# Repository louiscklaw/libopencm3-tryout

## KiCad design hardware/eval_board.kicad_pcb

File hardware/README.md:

### check list
debug port
screen text painting

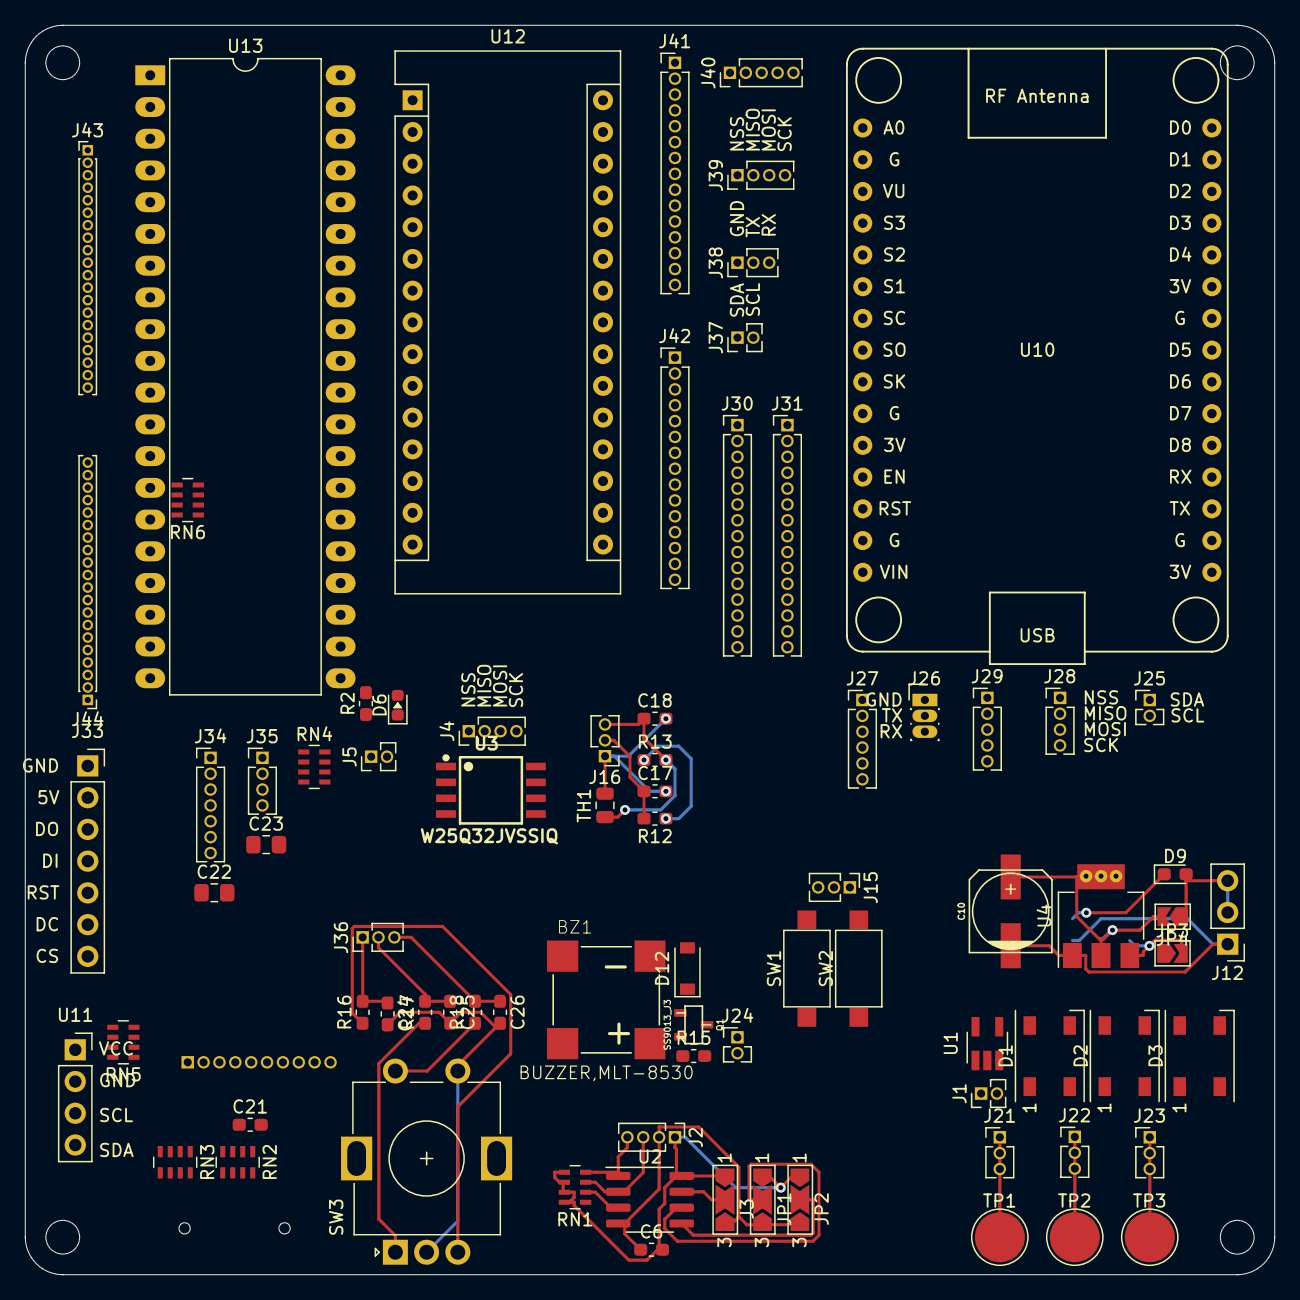
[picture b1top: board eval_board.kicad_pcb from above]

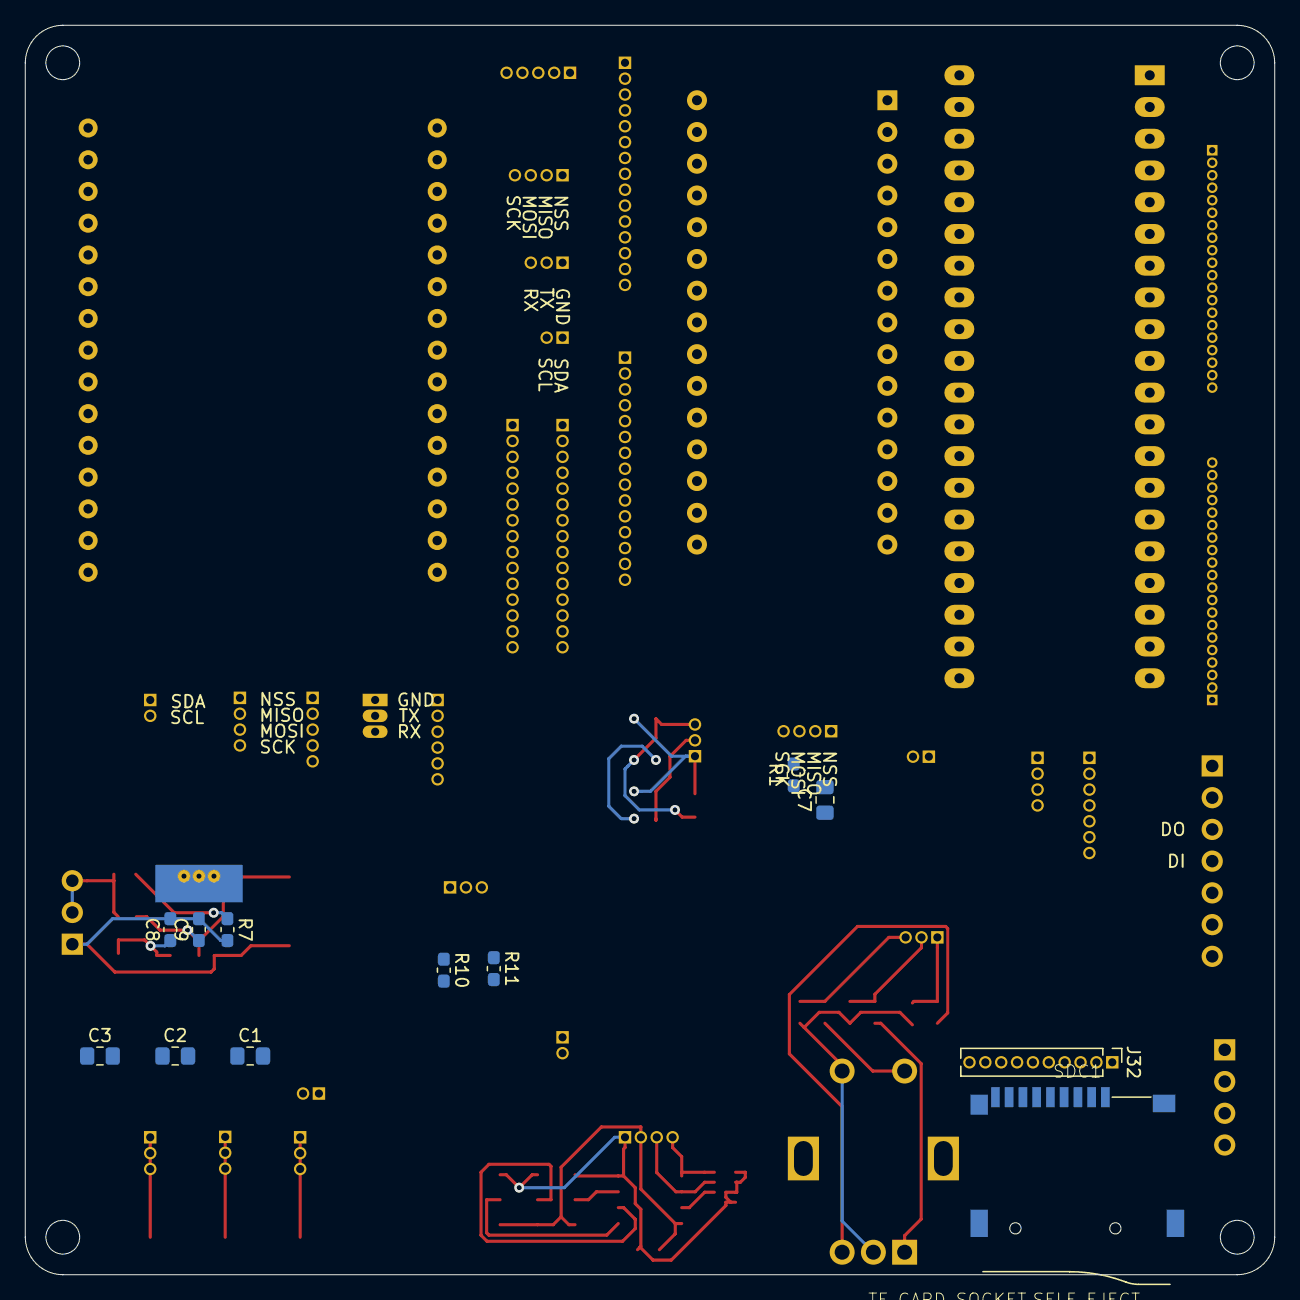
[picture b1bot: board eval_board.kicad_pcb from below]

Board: 2 copper layers, 100.0 x 100.0 mm, 97 parts (12 on the bottom side), 91 nets.

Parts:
BZ1: BUZZER,MLT-8530; MLT-8530
C1, C2, C3, C7, C22, C23: C106,0805; C_0805_2012Metric_Pad1.15x1.40mm_HandSolder
C6, C17, C18: C106,0603; C_0603_1608Metric_Pad1.05x0.95mm_HandSolder
C8, C9, C24, C25, C26: C104,0603; C_0603_1608Metric_Pad1.05x0.95mm_HandSolder
C10: CP47uf,50V; c_elec_6.3x7.7
C21: C475,0805; C_0603_1608Metric_Pad1.05x0.95mm_HandSolder
D1, D2, D3: WS2812B; LED_WS2812B_PLCC4_5.0x5.0mm_P3.2mm
D6: LED_GREEN,0603; LED_0603_1608Metric
D9: LED_GREEN,0603; LED_0603_1608Metric_Pad1.05x0.95mm_HandSolder
D12: D_1N4148_T4; D_SOD-123
H1, H2, H3, H4: MountingHole; MountingHole_2.7mm_M2.5,rpi_like
J1: WS2812_HEADER; PinHeader_1x02_P1.27mm_Vertical
J2, J35: OLED_I2C_HEADER; PinHeader_1x04_P1.27mm_Vertical
J3: A0_SEL; SolderJumper-3_P2.0mm_Open_TrianglePad1.0x1.5mm_NumberLabels
J4, J28, J39: SPI_HEADER; SPI_DEBUG
J5: BLINK_HEADER; PinHeader_1x02_P1.27mm_Vertical
J12: Conn_01x03; PinHeader_1x03_P2.54mm_Vertical
J15: BTN_HEADER; PinHeader_1x03_P1.27mm_Vertical
J16: ADC_HEADER; PinHeader_1x03_P1.27mm_Vertical
J21: GND; PinHeader_1x03_P1.27mm_Vertical
J22: 5V; PinHeader_1x03_P1.27mm_Vertical
J23: 3V3; PinHeader_1x03_P1.27mm_Vertical
J24: BUZZER_HEADER; PinHeader_1x02_P1.27mm_Vertical
J25: I2C_DEBUG
J26: TTL_HEADER; TTL_TERMINAL_1.27mm
J27: SDCARD_HEADER
J29, J40: OLED_HEADER; PinHeader_1x05_P1.27mm_Vertical
J30: NODEMCU_HEADER1; PinHeader_1x15_P1.27mm_Vertical
J31: NODEMCU_HEADER2; PinHeader_1x15_P1.27mm_Vertical
J32: sdcard_header; SDCARD_HEADER_10PIN
J33: SSD1306-OLED-SPI; CONN_SPI_SSD1306
J34: OLED_SPI_HEADER; PinHeader_1x07_P1.27mm_Vertical
J36: ROT_ENC_HEADER; PinHeader_1x03_P1.27mm_Vertical
J37: I2C_HEADER; I2C_DEBUG
J38: TTL_HEADER
J41: ARDUINO_HEADER1; PinHeader_1x15_P1.27mm_Vertical
J42: ARDUINO_HEADER2; PinHeader_1x15_P1.27mm_Vertical
J43: STM32_2_DEBUG1; PinHeader_1x20_P1.00mm_Vertical
J44: STM32_2_DEBUG2; PinHeader_1x20_P1.00mm_Vertical
JP1: A1_SEL; SolderJumper-3_P2.0mm_Open_TrianglePad1.0x1.5mm_NumberLabels
JP2: A2_SEL; SolderJumper-3_P2.0mm_Open_TrianglePad1.0x1.5mm_NumberLabels
JP3: PWR_SRC; SolderJumper-2_P1.3mm_Open_TrianglePad1.0x1.5mm
JP4: PWR_OUT; SolderJumper-2_P1.3mm_Open_TrianglePad1.0x1.5mm
Q1: SS9013_J3; 9013,J3,SOT23
R1, R10, R11: R103,0603; R_0603_1608Metric_Pad1.05x0.95mm_HandSolder
R2, R15: R471,0603; R_0603_1608Metric_Pad1.05x0.95mm_HandSolder
R7: R102,0603; R_0603_1608Metric_Pad1.05x0.95mm_HandSolder
R12, R13: R472,0603; R_0603_1608Metric_Pad1.05x0.95mm_HandSolder
R16, R17, R18: R273,0603; R_0603_1608Metric_Pad1.05x0.95mm_HandSolder
RN1, RN2, RN3, RN4, RN5, RN6: R_Pack04; R_Array_Concave_4x0603
SDC1: TF_CARD_SOCKET,SELF_EJECT; SUNTECH_ST-TF-003A
SW1, SW2: SW_RESET,2_leg,SMD; SW_SPST_CK_RS282G05A3
SW3: EC11_VERTICAL; RotaryEncoder_Alps_EC11E_Vertical_H20mm
TH1: Thermistor_NTC,0805; R_0805_2012Metric
TP1, TP2, TP3: TestPoint; TestPoint_Pad_D4.0mm
U1: 74AHCT1G125; SOT-23-5_HandSoldering
U2: LM75; SOP-8_3.76x4.96mm_P1.27mm
U3: W25Q32JVSSIQ
U4: AMS1117-3.3; AMS1117_SOT-223
U10: nodemcu; NodeMCU1.0(12-E)
U11: SSD1306-OLED-I2C; CONN_I2C_SSD1306
U12: arduino_nano_v3; Arduino_Nano
U13: bluepill-stm32f103c8t6; DIP-40_W15.24mm_LongPads

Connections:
+3V3: BZ1.P, C6.2, C7.2, C21.1, C22.2, C23.2, D9.2, D12.1, J2.1, J3.1, J12.2, J12.3, J23.1, J23.2, J23.3, J30.11, J31.6, J31.15, J32.VDD, J33.5V, J34.1, J35.1, J43.18, J44.1, JP1.1, JP2.1, JP4.1, R1.1, R2.1, R10.1, R12.1, R13.1, RN1.5, RN1.6, RN1.7, RN1.8, RN2.5, RN2.6, RN2.7, RN2.8, RN3.5, RN3.6, RN3.7, RN3.8, RN4.5, RN4.6, RN4.7, RN4.8, RN5.5, RN5.6, RN5.7, RN5.8, RN6.5, RN6.6, RN6.7, RN6.8, SDC1.4, SW1.2, TP3.1, U2.8, U3.3, U3.7, U3.8, U10.11, U10.16, U10.25, U11.VCC, U13.20, U13.38
+5V: C1.2, C2.2, C3.2, D1.1, D2.1, D3.1, J22.1, J22.2, J22.3, J42.1, J42.4, J44.3, TP2.1, U1.5, U12.27, U12.30, U13.18
/A_IN0: C17.1, J16.2, J43.5, R12.2, U13.25
/A_IN1: C18.1, J16.3, J43.6, R13.2, TH1.1, U13.26
/BTN_PULL_DN: J15.3, J43.8, R11.2, SW1.1, U13.28
/BTN_PULL_UP: J15.2, J43.13, R10.2, SW2.1, U13.33
/BUZZER_IN: J24.1, J44.13, R15.2, U13.8
/DEBUG_LED: D6.1, J5.2, J44.9, U13.12
/LORA_DIO0: J44.16, U13.5
/LORA_RST: J44.18, U13.3
/MISO: J4.MISO, J28.MISO, J31.9, J39.MISO, J41.15, J43.11, U3.2, U10.22, U12.15, U13.31
/MOSI: J4.MOSI, J28.MOSI, J29.1, J31.10, J33.DI, J34.4, J39.MOSI, J40.1, J41.14, J43.12, RN4.4, U3.5, U10.21, U12.14, U13.32
/OLED_DC: J33.DC, J34.6, J43.14, RN4.3, U13.34
/OLED_RST: J33.RST, J34.5, J44.8, U13.13
/PWM_IN: J44.11, U13.10
/ROT_ENC_A: C24.1, J36.1, J44.5, R16.2, U13.16
/ROT_ENC_B: C25.1, J36.2, J44.4, R17.2, U13.17
/ROT_ENC_SW: C26.1, J36.3, J43.15, R18.2, U13.35
/RX: J44.14, U13.7
/SCK: J4.SCK, J28.SCK, J29.2, J31.8, J33.DO, J34.3, J39.SCK, J40.2, J42.15, J43.10, RN4.2, U3.6, U10.23, U12.16, U13.30
/SCL: J2.3, J25.SCL, J31.2, J35.3, J37.SCL, J42.7, J44.7, RN1.3, RN5.2, RN6.2, U2.2, U10.29, U11.SCL, U12.24, U13.14
/SDA: J2.4, J25.SDA, J31.1, J37.SDA, J42.8, J44.6, RN1.4, RN6.1, U2.1, U10.30, U12.23, U13.15
/SDCLK: J27.SDCLK, J30.9, J32.CLK, RN2.2, SDC1.5, U10.9
/SDCMD: J27.SDCMD, J30.7, J32.CMD, RN2.4, SDC1.3, U10.7
/SDD0: J27.SDD0, J30.8, J32.DAT0, RN3.2, SDC1.7, U10.8
/SDD1: J27.SDD1, J30.6, J32.CAT1, RN3.1, SDC1.8, U10.6
/SDD2: J27.SDD2, J30.5, J32.DAT2, RN3.4, SDC1.1, U10.5
/SDD3: J27.SDD3, J30.4, J32.DAT3, RN3.3, SDC1.2, U10.4
/SS_ARDUINO: J39.NSS, J41.13, J44.19, U12.13, U13.2
/SS_ESP: J28.NSS, J31.11, J44.20, U10.20, U13.1
/SS_LORA: J44.12, U13.9
/SS_OLED: J33.CS, J34.7, J44.10, RN4.1, U13.11
/SS_STM32: J43.9, U13.29
/SS_W25Q32: J4.NSS, J44.17, R1.2, U3.1, U13.4
/TX: J44.15, U13.6
/WS2812_OUT: J1.2, J43.16, U1.2, U13.36
/arduino_nano/3V3: J42.14, U12.17
/arduino_nano/A0: J42.12, U12.19
/arduino_nano/A1: J42.11, U12.20
/arduino_nano/A2: J42.10, U12.21
/arduino_nano/A3: J42.9, U12.22
/arduino_nano/A6: J42.6, U12.25
/arduino_nano/A7: J42.5, U12.26
/arduino_nano/AREF: J42.13, U12.18
/arduino_nano/D0: J38.RX, J41.2, U12.2
/arduino_nano/D1: J38.TX, J41.1, U12.1
/arduino_nano/D2: J41.5, U12.5
/arduino_nano/D3: J41.6, U12.6
/arduino_nano/D7: J41.10, U12.10
/arduino_nano/D8: J41.11, U12.11
/arduino_nano/D9: J41.12, U12.12
/arduino_nano/OLED_DC: J40.3, J41.7, U12.7
/arduino_nano/OLED_RST: J40.4, J41.8, U12.8
/arduino_nano/OLED_SS: J40.5, J41.9, U12.9
/arduino_nano/RST: J41.3, J42.3, U12.3, U12.28
/bluepill/NRST: J43.17, U13.37
/bluepill/PA2: J43.7, U13.27
/bluepill/PC13: J43.2, U13.22
/bluepill/PC14: J43.3, U13.23
/bluepill/PC15: J43.4, U13.24
/bluepill/VBAT: J43.1, U13.21
/nodemcu/A0: J30.1, U10.1
/nodemcu/EN: J30.12, U10.12
/nodemcu/OLED_DC: J29.3, J31.3, U10.28
/nodemcu/OLED_RST: J29.4, J31.4, U10.27
/nodemcu/OLED_SS: J29.5, J31.5, U10.26
/nodemcu/RST: J30.13, U10.13
/nodemcu/RSV_2: J30.2, U10.2
/nodemcu/RSV_3: J30.3, U10.3
/nodemcu/RX: J26.RX, J31.12, U10.19
/nodemcu/TX: J26.TX, J31.13, U10.18
/nodemcu/VIN: J30.15, U10.15
/oled.sch/OLED_I2C_SDA: J35.4, RN5.1, U11.SDA
GND: C1.1, C2.1, C3.1, C6.1, C7.1, C8.2, C9.2, C10.2, C17.2, C18.2, C21.2, C22.1, C23.1, C24.2, C25.2, C26.2, D1.3, D2.3, D3.3, J1.1, J2.2, J3.3, J5.1, J12.1, J15.1, J16.1, J21.1, J21.2, J21.3, J24.2, J26.GND, J30.10, J30.14, J31.7, J31.14, J32.GND, J32.VSS, J33.GND, J34.2, J35.2, J38.GND, J41.4, J42.2, J43.19, J43.20, J44.2, JP1.3, JP2.3, Q1.2, R7.2, R11.1, SDC1.6, SDC1.G, SW2.2, SW3.C, SW3.E, TH1.2, TP1.1, U1.1, U1.3, U2.4, U3.4, U4.1, U10.10, U10.14, U10.17, U10.24, U11.GND, U12.4, U12.29, U13.19, U13.39, U13.40
unnamed: BZ1.N, D12.2, Q1.3
unnamed: C8.1, JP3.2, U4.3
unnamed: C9.1, C10.1, JP4.2, U4.2
unnamed: D1.2, D2.4
unnamed: D1.4, U1.4
unnamed: D2.2, D3.4
unnamed: D6.2, R2.2
unnamed: D9.1, R7.1
unnamed: J3.2, U2.7
unnamed: J32.CD, SDC1.9
unnamed: JP1.2, U2.6
unnamed: JP2.2, U2.5
unnamed: Q1.1, R15.1
unnamed: R16.1, SW3.B
unnamed: R17.1, SW3.A
unnamed: R18.1, SW3.D
unnamed: RN1.2, U2.3

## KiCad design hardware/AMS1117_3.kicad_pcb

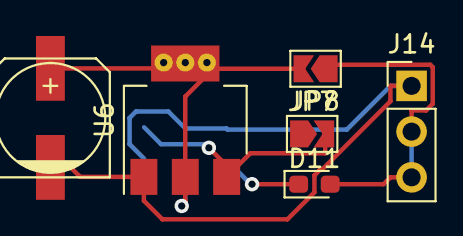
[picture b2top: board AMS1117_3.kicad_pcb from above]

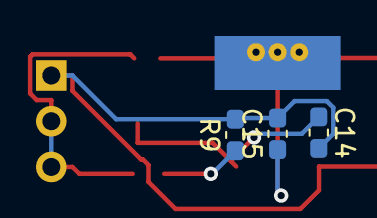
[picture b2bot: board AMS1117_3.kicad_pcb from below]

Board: 2 copper layers, 9 parts (3 on the bottom side), 5 nets.

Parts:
C14, C15: C104,0603; C_0603_1608Metric_Pad1.05x0.95mm_HandSolder
C16: CP47uf,50V; c_elec_6.3x7.7
D11: LED_GREEN,0603; LED_0603_1608Metric_Pad1.05x0.95mm_HandSolder
J14: Va_header; PinHeader_1x03_P2.54mm_Vertical
JP7: PWR_SRC; SolderJumper-2_P1.3mm_Open_TrianglePad1.0x1.5mm
JP8: PWR_OUT; SolderJumper-2_P1.3mm_Open_TrianglePad1.0x1.5mm
R9: R102,0603; R_0603_1608Metric_Pad1.05x0.95mm_HandSolder
U6: AMS1117-3.3; AMS1117_SOT-223

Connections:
GND: C14.2, C15.2, C16.2, J14.1, R9.2, U6.1
unnamed: C14.1, JP7.2, U6.3
unnamed: C15.1, C16.1, JP8.2, U6.2
unnamed: D11.1, R9.1
Vc: D11.2, J14.2, J14.3, JP8.1

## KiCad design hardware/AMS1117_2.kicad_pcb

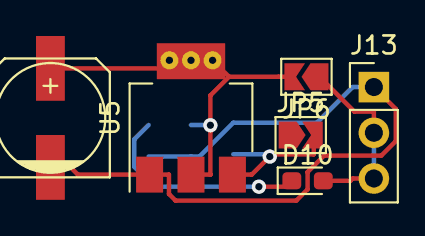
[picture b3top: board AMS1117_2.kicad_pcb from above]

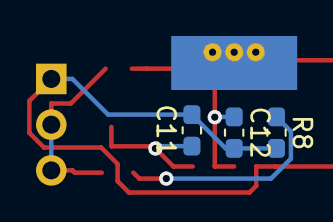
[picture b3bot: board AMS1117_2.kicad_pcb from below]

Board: 2 copper layers, 9 parts (3 on the bottom side), 5 nets.

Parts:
C11, C12: C104,0603; C_0603_1608Metric_Pad1.05x0.95mm_HandSolder
C13: CP47uf,50V; c_elec_6.3x7.7
D10: LED_GREEN,0603; LED_0603_1608Metric_Pad1.05x0.95mm_HandSolder
J13: Conn_01x03; PinHeader_1x03_P2.54mm_Vertical
JP5: PWR_SRC; SolderJumper-2_P1.3mm_Open_TrianglePad1.0x1.5mm
JP6: PWR_OUT; SolderJumper-2_P1.3mm_Open_TrianglePad1.0x1.5mm
R8: R102,0603; R_0603_1608Metric_Pad1.05x0.95mm_HandSolder
U5: AMS1117-3.3; AMS1117_SOT-223

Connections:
GND: C11.2, C12.2, C13.2, J13.1, R8.2, U5.1
unnamed: C11.1, JP5.2, U5.3
unnamed: C12.1, C13.1, JP6.2, U5.2
unnamed: D10.1, R8.1
Vb: D10.2, J13.2, J13.3, JP6.1

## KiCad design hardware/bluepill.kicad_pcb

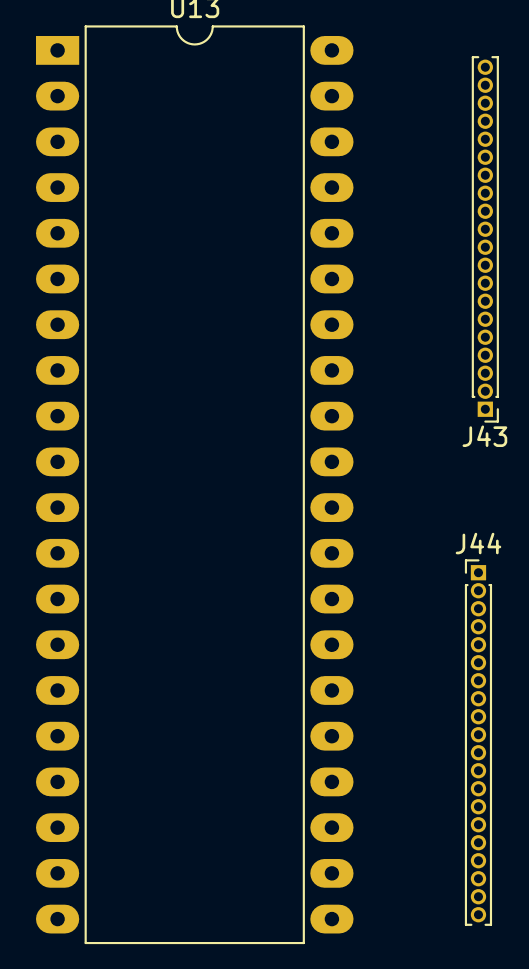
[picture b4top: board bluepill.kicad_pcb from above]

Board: 2 copper layers, 4 parts (1 on the bottom side), 37 nets, no tracks yet.

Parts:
J43: STM32_2_DEBUG1; PinHeader_1x20_P1.00mm_Vertical
J44: STM32_2_DEBUG2; PinHeader_1x20_P1.00mm_Vertical
RN6: R_Pack04; R_Array_Concave_4x0603
U13: bluepill-stm32f103c8t6; DIP-40_W15.24mm_LongPads

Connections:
+3V3: J43.18, J44.1, RN6.5, RN6.6, RN6.7, RN6.8, U13.20, U13.38
+5V: J44.3, U13.18
/A_IN0: J43.5, U13.25
/A_IN1: J43.6, U13.26
/BTN_PULL_DN: J43.8, U13.28
/BTN_PULL_UP: J43.13, U13.33
/BUZZER: J44.13, U13.8
/DEBUG_LED: J44.9, U13.12
/LORA_DIO0: J44.16, U13.5
/LORA_RST: J44.18, U13.3
/MISO: J43.11, U13.31
/MOSI: J43.12, U13.32
/NRST: J43.17, U13.37
/OLED_DC: J43.14, U13.34
/OLED_RST: J44.8, U13.13
/OLED_SS: J44.10, U13.11
/PA2: J43.7, U13.27
/PC13: J43.2, U13.22
/PC14: J43.3, U13.23
/PC15: J43.4, U13.24
/PWM: J44.11, U13.10
/ROT_ENC_A: J44.5, U13.16
/ROT_ENC_B: J44.4, U13.17
/ROT_ENC_SW: J43.15, U13.35
/RX: J44.14, U13.7
/SCK: J43.10, U13.30
/SCL: J44.7, RN6.2, U13.14
/SDA: J44.6, RN6.1, U13.15
/SS: J43.9, U13.29
/SS_ARDUINO: J44.19, U13.2
/SS_ESP: J44.20, U13.1
/SS_LORA: J44.12, U13.9
/SS_W25Q32: J44.17, U13.4
/TX: J44.15, U13.6
/VBAT: J43.1, U13.21
/WS2812_OUT: J43.16, U13.36
GND: J43.19, J43.20, J44.2, U13.19, U13.39, U13.40

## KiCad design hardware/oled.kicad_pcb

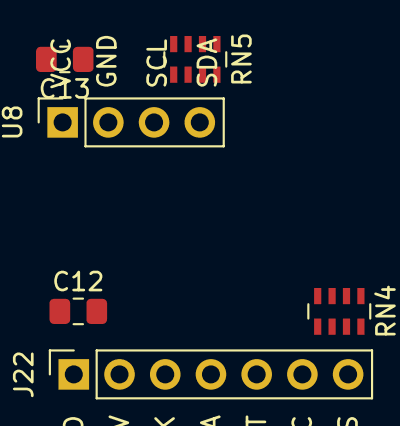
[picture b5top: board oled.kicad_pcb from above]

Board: 2 copper layers, 6 parts (0 on the bottom side), 6 nets, no tracks yet.

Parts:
C12, C13: C106,0805; C_0805_2012Metric_Pad1.15x1.40mm_HandSolder
J22: SSD1306-OLED-SPI; CONN_SPI_SSD1306
RN4, RN5: R_Pack04; R_Array_Concave_4x0603
U8: SSD1306-OLED-I2C; CONN_I2C_SSD1306

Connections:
+3V3: C12.2, C13.2, J22.5V, RN4.5, RN4.6, RN4.7, RN4.8, RN5.5, RN5.6, RN5.7, RN5.8, U8.VCC
/DC: J22.DC, RN4.3
/SCL: RN5.2, U8.SCL
/SDA: RN5.1, U8.SDA
/SS: J22.CS, RN4.1
GND: C12.1, C13.1, J22.GND, U8.GND

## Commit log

2019-05-14 working USB write example,
2019-05-14 update,
2019-05-14 update datasheet,
2019-05-21 update for CH340T,
2019-05-21 update fixing library,
2019-05-21 update power schematic,
2019-05-21 update button sch,
2019-05-22 update for add capacitor,
2019-05-22 update for adding arduino nano,
2019-05-28 update for gitignore,
2019-05-28 update for blink example for bluepill,
2019-05-29 update footprint,
2019-05-29 update sdcard header,
2019-06-29 update fabfile,
2020-05-06 ci: init travis token,
2020-05-06 ci: init travis build config,
2020-05-15 ci: update travis credentials.yml,
